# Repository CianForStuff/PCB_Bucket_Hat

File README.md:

# PCB_Bucket_Hat
Cute little hat made of a flex printed circuit board

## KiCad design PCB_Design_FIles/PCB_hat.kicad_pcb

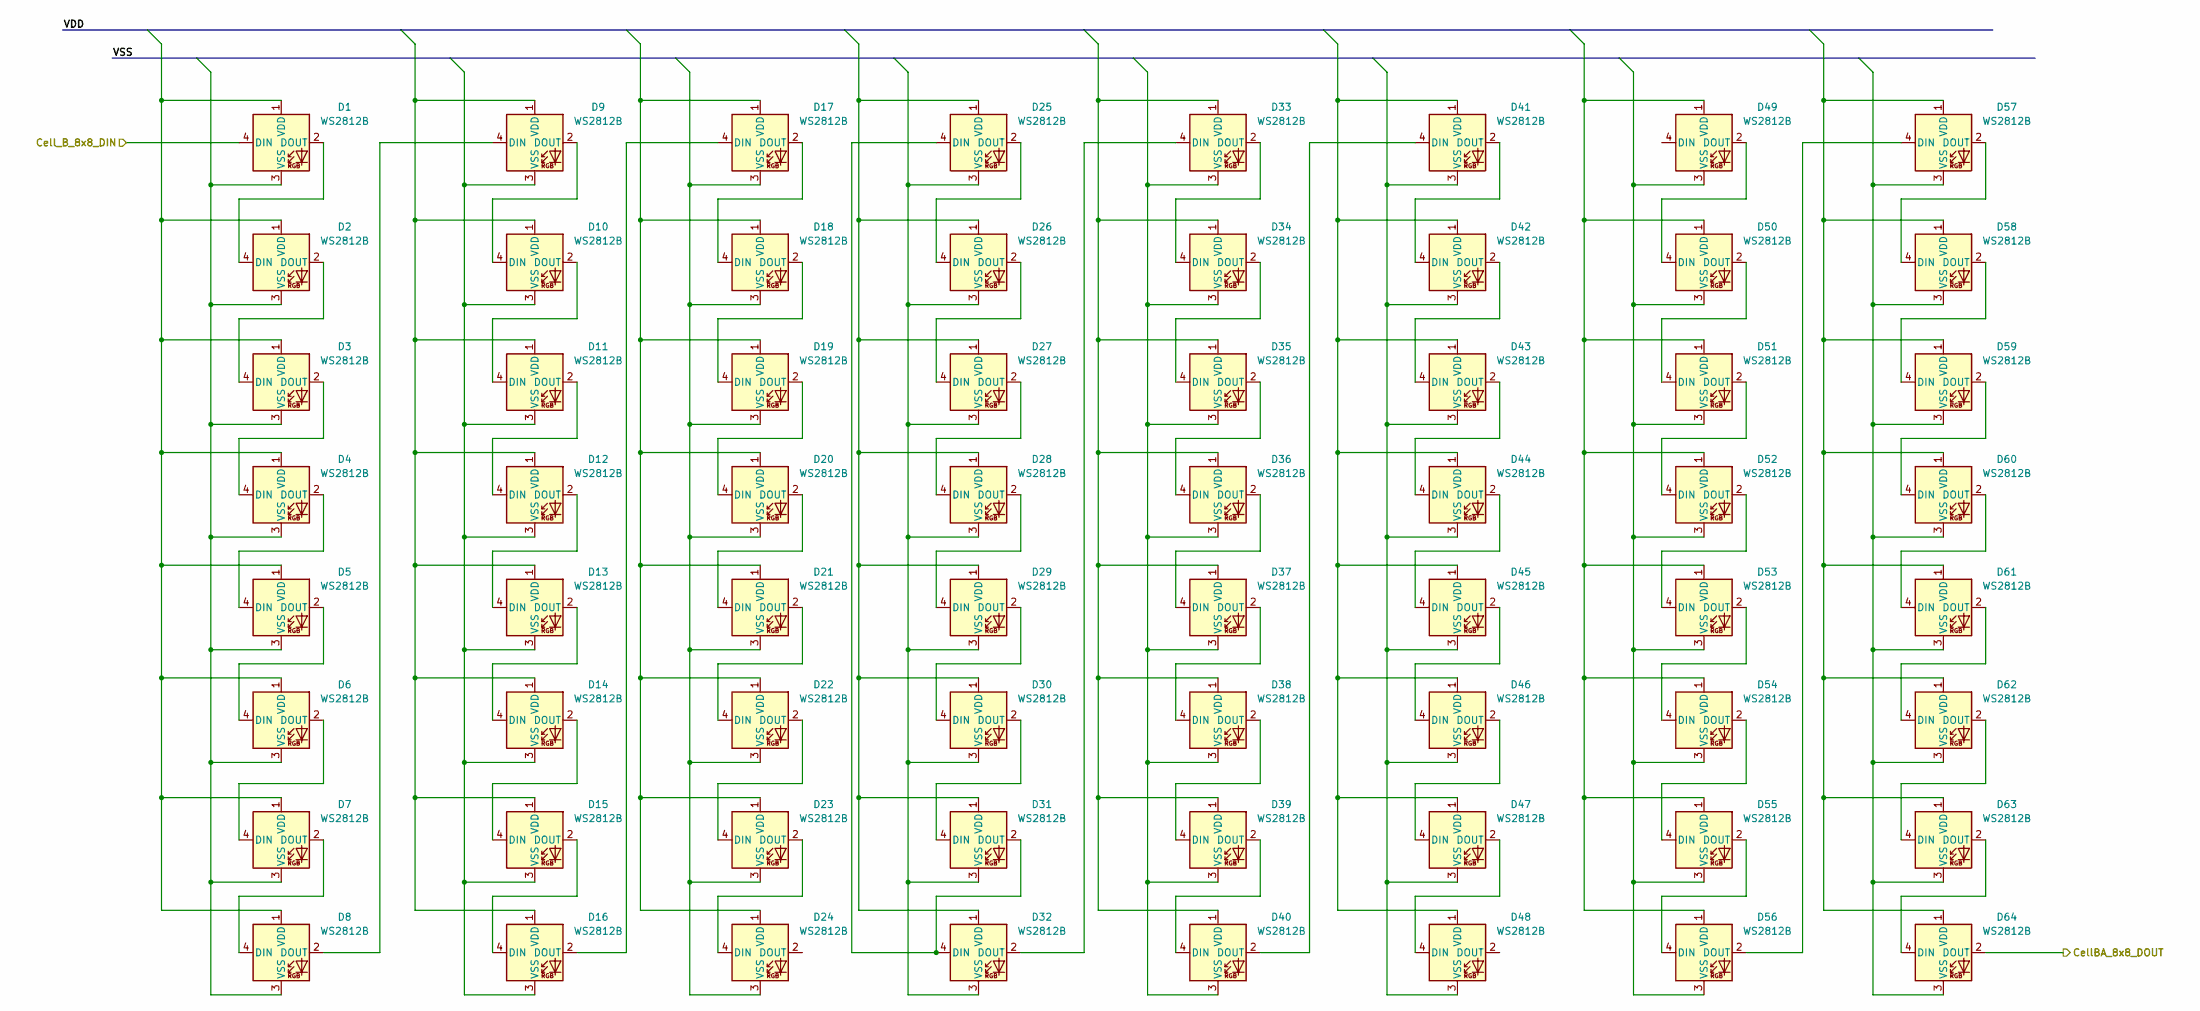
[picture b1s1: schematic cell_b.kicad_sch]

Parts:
D1, D2, D3, D4, D5, D6, D7, D8, D9, D10, D11, D12, D13, D14, D15, D16, D17, D18, D19, D20, D21, D22, D23, D24, D25, D26, D27, D28, D29, D30, D31, D32, D33, D34, D35, D36, D37, D38, D39, D40, D41, D42, D43, D44, D45, D46, D47, D48, D49, D50, D51, D52, D53, D54, D55, D56, D57, D58, D59, D60, D61, D62, D63, D64: WS2812B; LED_WS2812B_PLCC4_5.0x5.0mm_P3.2mm

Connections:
/Cell_A/Cell_A_8x8_DOUT: D1.4 (DIN); also elsewhere on the board
/Cell_B/CellBA_8x8_DOUT: D64.2 (DOUT)
unnamed: D1.2 (DOUT), D2.4 (DIN)
unnamed: D1.1 (VDD), D2.1 (VDD), D3.1 (VDD), D4.1 (VDD), D5.1 (VDD), D6.1 (VDD), D7.1 (VDD), D8.1 (VDD)
unnamed: D1.3 (VSS), D2.3 (VSS), D3.3 (VSS), D4.3 (VSS), D5.3 (VSS), D6.3 (VSS), D7.3 (VSS), D8.3 (VSS)
unnamed: D2.2 (DOUT), D3.4 (DIN)
unnamed: D3.2 (DOUT), D4.4 (DIN)
unnamed: D4.2 (DOUT), D5.4 (DIN)
unnamed: D5.2 (DOUT), D6.4 (DIN)
unnamed: D6.2 (DOUT), D7.4 (DIN)
unnamed: D7.2 (DOUT), D8.4 (DIN)
unnamed: D8.2 (DOUT), D9.4 (DIN)
unnamed: D9.2 (DOUT), D10.4 (DIN)
unnamed: D10.2 (DOUT), D11.4 (DIN)
unnamed: D9.1 (VDD), D10.1 (VDD), D11.1 (VDD), D12.1 (VDD), D13.1 (VDD), D14.1 (VDD), D15.1 (VDD), D16.1 (VDD)
unnamed: D9.3 (VSS), D10.3 (VSS), D11.3 (VSS), D12.3 (VSS), D13.3 (VSS), D14.3 (VSS), D15.3 (VSS), D16.3 (VSS)
unnamed: D11.2 (DOUT), D12.4 (DIN)
unnamed: D12.2 (DOUT), D13.4 (DIN)
unnamed: D13.2 (DOUT), D14.4 (DIN)
unnamed: D14.2 (DOUT), D15.4 (DIN)
unnamed: D15.2 (DOUT), D16.4 (DIN)
unnamed: D16.2 (DOUT), D17.4 (DIN)
unnamed: D17.2 (DOUT), D18.4 (DIN)
unnamed: D17.1 (VDD), D18.1 (VDD), D19.1 (VDD), D20.1 (VDD), D21.1 (VDD), D22.1 (VDD), D23.1 (VDD), D24.1 (VDD)
unnamed: D17.3 (VSS), D18.3 (VSS), D19.3 (VSS), D20.3 (VSS), D21.3 (VSS), D22.3 (VSS), D23.3 (VSS), D24.3 (VSS)
unnamed: D18.2 (DOUT), D19.4 (DIN)
unnamed: D19.2 (DOUT), D20.4 (DIN)
unnamed: D20.2 (DOUT), D21.4 (DIN)
unnamed: D21.2 (DOUT), D22.4 (DIN)
unnamed: D22.2 (DOUT), D23.4 (DIN)
unnamed: D23.2 (DOUT), D24.4 (DIN)
unnamed: D25.4 (DIN), D31.2 (DOUT), D32.4 (DIN)
unnamed: D25.2 (DOUT), D26.4 (DIN)
unnamed: D25.1 (VDD), D26.1 (VDD), D27.1 (VDD), D28.1 (VDD), D29.1 (VDD), D30.1 (VDD), D31.1 (VDD), D32.1 (VDD)
unnamed: D25.3 (VSS), D26.3 (VSS), D27.3 (VSS), D28.3 (VSS), D29.3 (VSS), D30.3 (VSS), D31.3 (VSS), D32.3 (VSS)
unnamed: D26.2 (DOUT), D27.4 (DIN)
unnamed: D27.2 (DOUT), D28.4 (DIN)
unnamed: D28.2 (DOUT), D29.4 (DIN)
unnamed: D29.2 (DOUT), D30.4 (DIN)
unnamed: D30.2 (DOUT), D31.4 (DIN)
unnamed: D32.2 (DOUT), D33.4 (DIN)
unnamed: D33.2 (DOUT), D34.4 (DIN)
unnamed: D33.1 (VDD), D34.1 (VDD), D35.1 (VDD), D36.1 (VDD), D37.1 (VDD), D38.1 (VDD), D39.1 (VDD), D40.1 (VDD)
unnamed: D33.3 (VSS), D34.3 (VSS), D35.3 (VSS), D36.3 (VSS), D37.3 (VSS), D38.3 (VSS), D39.3 (VSS), D40.3 (VSS)
unnamed: D34.2 (DOUT), D35.4 (DIN)
unnamed: D35.2 (DOUT), D36.4 (DIN)
unnamed: D36.2 (DOUT), D37.4 (DIN)
unnamed: D37.2 (DOUT), D38.4 (DIN)
unnamed: D38.2 (DOUT), D39.4 (DIN)
unnamed: D39.2 (DOUT), D40.4 (DIN)
unnamed: D40.2 (DOUT), D41.4 (DIN)
unnamed: D41.2 (DOUT), D42.4 (DIN)
unnamed: D41.1 (VDD), D42.1 (VDD), D43.1 (VDD), D44.1 (VDD), D45.1 (VDD), D46.1 (VDD), D47.1 (VDD), D48.1 (VDD)
unnamed: D41.3 (VSS), D42.3 (VSS), D43.3 (VSS), D44.3 (VSS), D45.3 (VSS), D46.3 (VSS), D47.3 (VSS), D48.3 (VSS)
unnamed: D42.2 (DOUT), D43.4 (DIN)
unnamed: D43.2 (DOUT), D44.4 (DIN)
unnamed: D44.2 (DOUT), D45.4 (DIN)
unnamed: D45.2 (DOUT), D46.4 (DIN)
unnamed: D46.2 (DOUT), D47.4 (DIN)
unnamed: D47.2 (DOUT), D48.4 (DIN)
unnamed: D49.2 (DOUT), D50.4 (DIN)
unnamed: D49.1 (VDD), D50.1 (VDD), D51.1 (VDD), D52.1 (VDD), D53.1 (VDD), D54.1 (VDD), D55.1 (VDD), D56.1 (VDD)
unnamed: D49.3 (VSS), D50.3 (VSS), D51.3 (VSS), D52.3 (VSS), D53.3 (VSS), D54.3 (VSS), D55.3 (VSS), D56.3 (VSS)
unnamed: D50.2 (DOUT), D51.4 (DIN)
unnamed: D51.2 (DOUT), D52.4 (DIN)
unnamed: D52.2 (DOUT), D53.4 (DIN)
unnamed: D53.2 (DOUT), D54.4 (DIN)
unnamed: D54.2 (DOUT), D55.4 (DIN)
unnamed: D55.2 (DOUT), D56.4 (DIN)
unnamed: D56.2 (DOUT), D57.4 (DIN)
unnamed: D57.2 (DOUT), D58.4 (DIN)
unnamed: D57.1 (VDD), D58.1 (VDD), D59.1 (VDD), D60.1 (VDD), D61.1 (VDD), D62.1 (VDD), D63.1 (VDD), D64.1 (VDD)
unnamed: D57.3 (VSS), D58.3 (VSS), D59.3 (VSS), D60.3 (VSS), D61.3 (VSS), D62.3 (VSS), D63.3 (VSS), D64.3 (VSS)
unnamed: D58.2 (DOUT), D59.4 (DIN)
unnamed: D59.2 (DOUT), D60.4 (DIN)
unnamed: D60.2 (DOUT), D61.4 (DIN)
unnamed: D61.2 (DOUT), D62.4 (DIN)
unnamed: D62.2 (DOUT), D63.4 (DIN)
unnamed: D63.2 (DOUT), D64.4 (DIN)

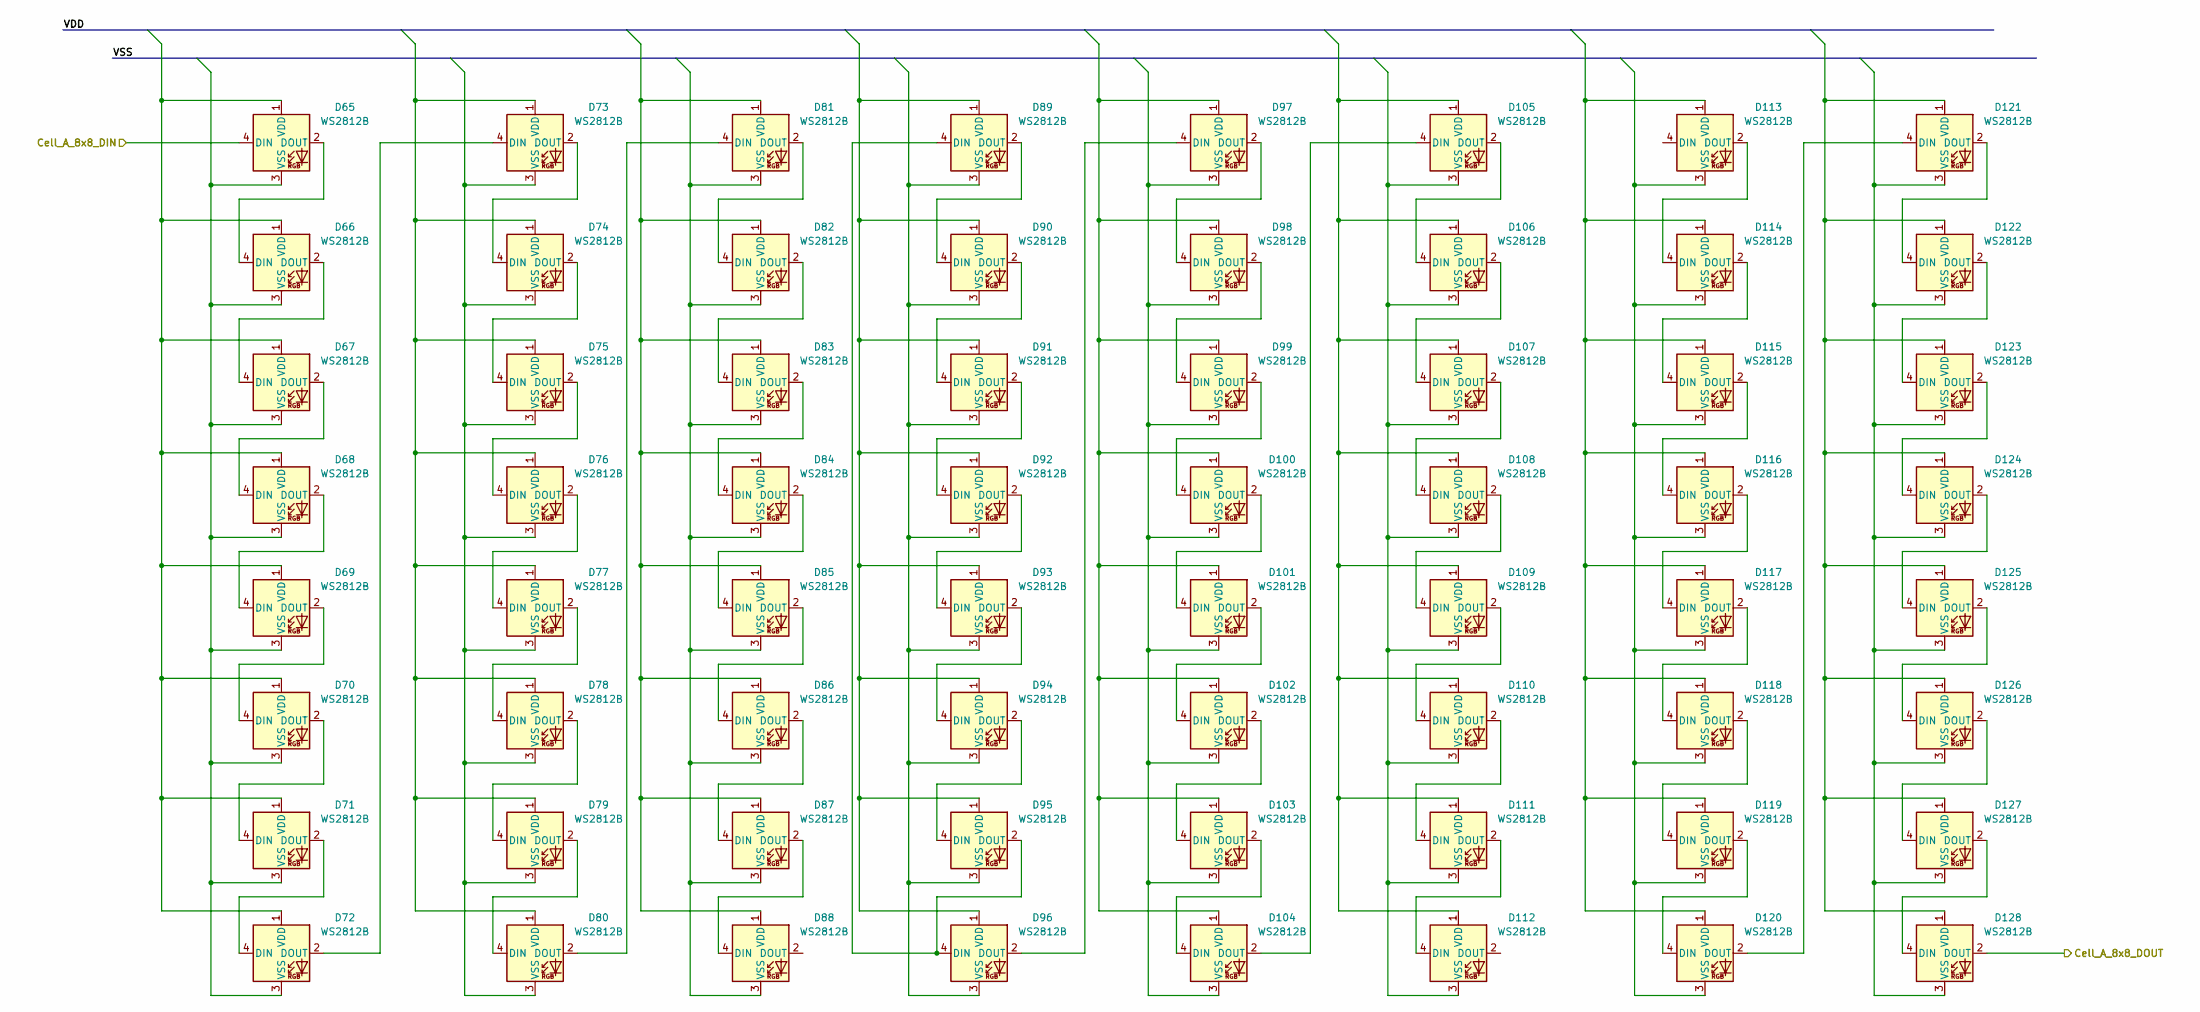
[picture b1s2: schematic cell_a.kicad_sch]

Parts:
D65, D66, D67, D68, D69, D70, D71, D72, D73, D74, D75, D76, D77, D78, D79, D80, D81, D82, D83, D84, D85, D86, D87, D88, D89, D90, D91, D92, D93, D94, D95, D96, D97, D98, D99, D100, D101, D102, D103, D104, D105, D106, D107, D108, D109, D110, D111, D112, D113, D114, D115, D116, D117, D118, D119, D120, D121, D122, D123, D124, D125, D126, D127, D128: WS2812B; LED_WS2812B_PLCC4_5.0x5.0mm_P3.2mm

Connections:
/Cell_A/Cell_A_8x8_DIN: D65.4 (DIN)
/Cell_A/Cell_A_8x8_DOUT: D128.2 (DOUT); also elsewhere on the board
unnamed: D65.2 (DOUT), D66.4 (DIN)
unnamed: D65.1 (VDD), D66.1 (VDD), D67.1 (VDD), D68.1 (VDD), D69.1 (VDD), D70.1 (VDD), D71.1 (VDD), D72.1 (VDD)
unnamed: D65.3 (VSS), D66.3 (VSS), D67.3 (VSS), D68.3 (VSS), D69.3 (VSS), D70.3 (VSS), D71.3 (VSS), D72.3 (VSS)
unnamed: D66.2 (DOUT), D67.4 (DIN)
unnamed: D67.2 (DOUT), D68.4 (DIN)
unnamed: D68.2 (DOUT), D69.4 (DIN)
unnamed: D69.2 (DOUT), D70.4 (DIN)
unnamed: D70.2 (DOUT), D71.4 (DIN)
unnamed: D71.2 (DOUT), D72.4 (DIN)
unnamed: D72.2 (DOUT), D73.4 (DIN)
unnamed: D73.2 (DOUT), D74.4 (DIN)
unnamed: D73.1 (VDD), D74.1 (VDD), D75.1 (VDD), D76.1 (VDD), D77.1 (VDD), D78.1 (VDD), D79.1 (VDD), D80.1 (VDD)
unnamed: D73.3 (VSS), D74.3 (VSS), D75.3 (VSS), D76.3 (VSS), D77.3 (VSS), D78.3 (VSS), D79.3 (VSS), D80.3 (VSS)
unnamed: D74.2 (DOUT), D75.4 (DIN)
unnamed: D75.2 (DOUT), D76.4 (DIN)
unnamed: D76.2 (DOUT), D77.4 (DIN)
unnamed: D77.2 (DOUT), D78.4 (DIN)
unnamed: D78.2 (DOUT), D79.4 (DIN)
unnamed: D79.2 (DOUT), D80.4 (DIN)
unnamed: D80.2 (DOUT), D81.4 (DIN)
unnamed: D81.2 (DOUT), D82.4 (DIN)
unnamed: D81.1 (VDD), D82.1 (VDD), D83.1 (VDD), D84.1 (VDD), D85.1 (VDD), D86.1 (VDD), D87.1 (VDD), D88.1 (VDD)
unnamed: D81.3 (VSS), D82.3 (VSS), D83.3 (VSS), D84.3 (VSS), D85.3 (VSS), D86.3 (VSS), D87.3 (VSS), D88.3 (VSS)
unnamed: D82.2 (DOUT), D83.4 (DIN)
unnamed: D83.2 (DOUT), D84.4 (DIN)
unnamed: D84.2 (DOUT), D85.4 (DIN)
unnamed: D85.2 (DOUT), D86.4 (DIN)
unnamed: D86.2 (DOUT), D87.4 (DIN)
unnamed: D87.2 (DOUT), D88.4 (DIN)
unnamed: D89.4 (DIN), D95.2 (DOUT), D96.4 (DIN)
unnamed: D89.2 (DOUT), D90.4 (DIN)
unnamed: D89.1 (VDD), D90.1 (VDD), D91.1 (VDD), D92.1 (VDD), D93.1 (VDD), D94.1 (VDD), D95.1 (VDD), D96.1 (VDD)
unnamed: D89.3 (VSS), D90.3 (VSS), D91.3 (VSS), D92.3 (VSS), D93.3 (VSS), D94.3 (VSS), D95.3 (VSS), D96.3 (VSS)
unnamed: D90.2 (DOUT), D91.4 (DIN)
unnamed: D91.2 (DOUT), D92.4 (DIN)
unnamed: D92.2 (DOUT), D93.4 (DIN)
unnamed: D93.2 (DOUT), D94.4 (DIN)
unnamed: D94.2 (DOUT), D95.4 (DIN)
unnamed: D96.2 (DOUT), D97.4 (DIN)
unnamed: D97.2 (DOUT), D98.4 (DIN)
unnamed: D98.2 (DOUT), D99.4 (DIN)
unnamed: D99.2 (DOUT), D100.4 (DIN)
unnamed: D100.2 (DOUT), D101.4 (DIN)
unnamed: D97.1 (VDD), D98.1 (VDD), D99.1 (VDD), D100.1 (VDD), D101.1 (VDD), D102.1 (VDD), D103.1 (VDD), D104.1 (VDD)
unnamed: D97.3 (VSS), D98.3 (VSS), D99.3 (VSS), D100.3 (VSS), D101.3 (VSS), D102.3 (VSS), D103.3 (VSS), D104.3 (VSS)
unnamed: D101.2 (DOUT), D102.4 (DIN)
unnamed: D102.2 (DOUT), D103.4 (DIN)
unnamed: D103.2 (DOUT), D104.4 (DIN)
unnamed: D104.2 (DOUT), D105.4 (DIN)
unnamed: D105.2 (DOUT), D106.4 (DIN)
unnamed: D105.1 (VDD), D106.1 (VDD), D107.1 (VDD), D108.1 (VDD), D109.1 (VDD), D110.1 (VDD), D111.1 (VDD), D112.1 (VDD)
unnamed: D105.3 (VSS), D106.3 (VSS), D107.3 (VSS), D108.3 (VSS), D109.3 (VSS), D110.3 (VSS), D111.3 (VSS), D112.3 (VSS)
unnamed: D106.2 (DOUT), D107.4 (DIN)
unnamed: D107.2 (DOUT), D108.4 (DIN)
unnamed: D108.2 (DOUT), D109.4 (DIN)
unnamed: D109.2 (DOUT), D110.4 (DIN)
unnamed: D110.2 (DOUT), D111.4 (DIN)
unnamed: D111.2 (DOUT), D112.4 (DIN)
unnamed: D113.2 (DOUT), D114.4 (DIN)
unnamed: D113.1 (VDD), D114.1 (VDD), D115.1 (VDD), D116.1 (VDD), D117.1 (VDD), D118.1 (VDD), D119.1 (VDD), D120.1 (VDD)
unnamed: D113.3 (VSS), D114.3 (VSS), D115.3 (VSS), D116.3 (VSS), D117.3 (VSS), D118.3 (VSS), D119.3 (VSS), D120.3 (VSS)
unnamed: D114.2 (DOUT), D115.4 (DIN)
unnamed: D115.2 (DOUT), D116.4 (DIN)
unnamed: D116.2 (DOUT), D117.4 (DIN)
unnamed: D117.2 (DOUT), D118.4 (DIN)
unnamed: D118.2 (DOUT), D119.4 (DIN)
unnamed: D119.2 (DOUT), D120.4 (DIN)
unnamed: D120.2 (DOUT), D121.4 (DIN)
unnamed: D121.2 (DOUT), D122.4 (DIN)
unnamed: D121.1 (VDD), D122.1 (VDD), D123.1 (VDD), D124.1 (VDD), D125.1 (VDD), D126.1 (VDD), D127.1 (VDD), D128.1 (VDD)
unnamed: D121.3 (VSS), D122.3 (VSS), D123.3 (VSS), D124.3 (VSS), D125.3 (VSS), D126.3 (VSS), D127.3 (VSS), D128.3 (VSS)
unnamed: D122.2 (DOUT), D123.4 (DIN)
unnamed: D123.2 (DOUT), D124.4 (DIN)
unnamed: D124.2 (DOUT), D125.4 (DIN)
unnamed: D125.2 (DOUT), D126.4 (DIN)
unnamed: D126.2 (DOUT), D127.4 (DIN)
unnamed: D127.2 (DOUT), D128.4 (DIN)

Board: 2 copper layers, 128 parts (0 on the bottom side), 155 nets, no tracks yet.

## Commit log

2025-07-02 init commit
